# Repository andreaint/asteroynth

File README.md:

# asteroynth
a playful open synth

List of components:
https://www.mouser.com/ProjectManager/ProjectDetail.aspx?AccessID=de6c1d56a3

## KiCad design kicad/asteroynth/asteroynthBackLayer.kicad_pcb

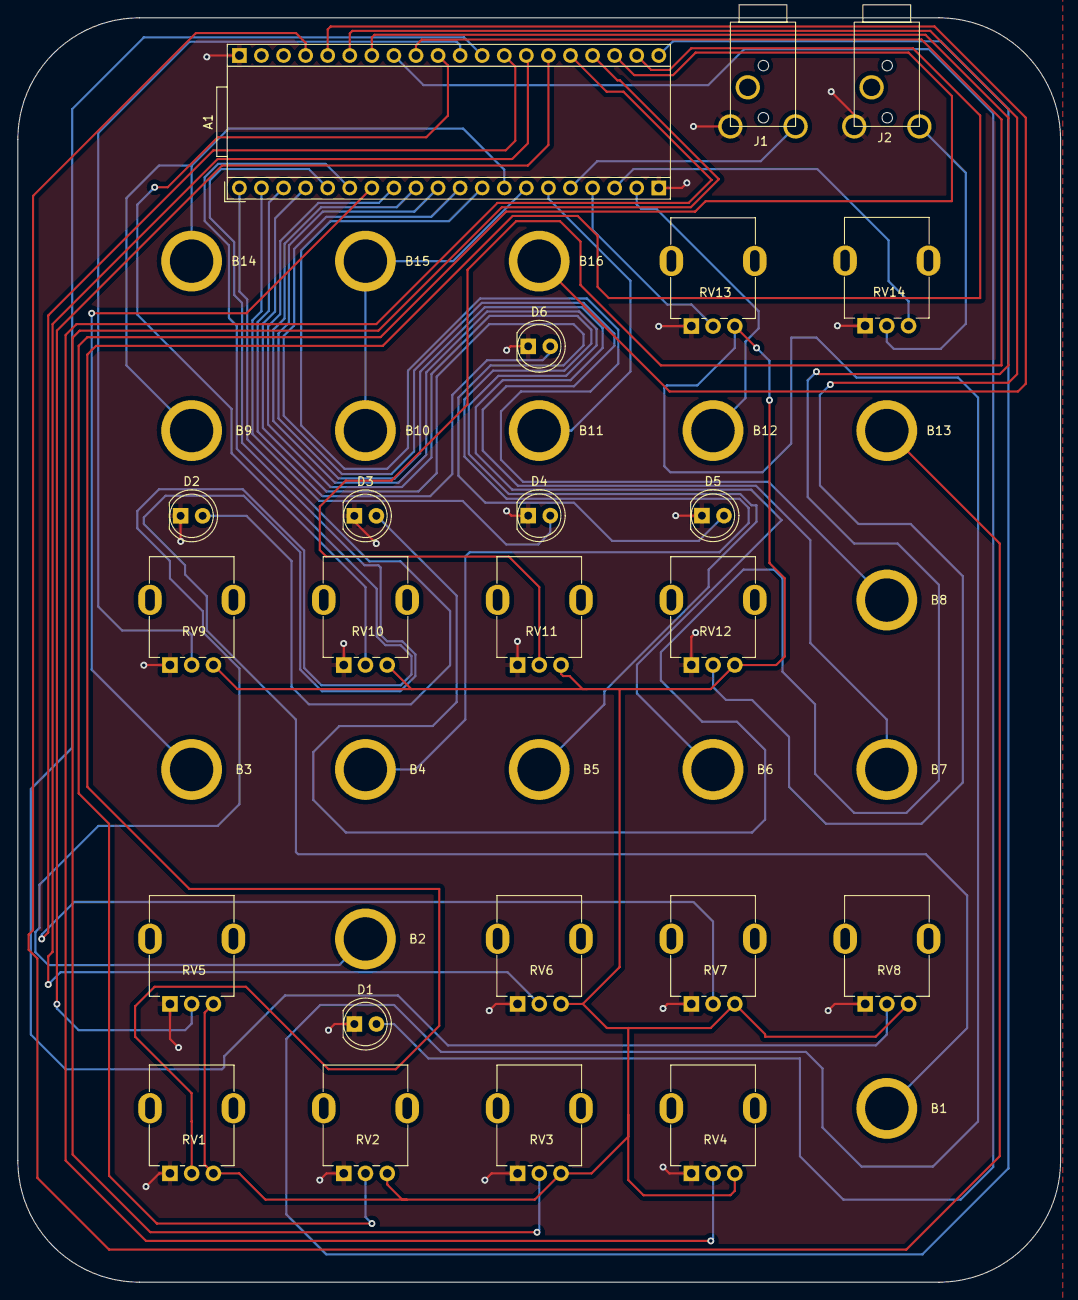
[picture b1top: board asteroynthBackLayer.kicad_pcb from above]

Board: 2 copper layers, 120.0 x 145.5 mm, 39 parts (0 on the bottom side), 38 nets.

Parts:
A1: Device_Audio_Electrosmith_Daisy_Seed_Rev4; Device_Audio_Electrosmith_Daisy_Seed
B1, B2, B3, B4, B5, B6, B7, B8, B9, B10, B11, B12, B13, B14, B15, B16: MyBananaJack; MyBananaJackFootprint
D1, D2, D3, D4, D5, D6: LED; LED_D5.0mm
J1: Audio In; audioJackFootprint
J2: Audio Out; audioJackFootprint
RV1, RV2, RV3, RV4, RV5, RV6, RV7, RV8, RV9, RV10, RV11, RV12, RV13, RV14: R_Potentiometer; MyPotType1Footprint

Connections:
+3V3: A1.21 (3V3_A), RV1.3, RV2.3, RV3.3, RV4.3, RV5.3, RV6.3, RV7.3, RV8.3, RV9.3, RV10.3, RV11.3, RV12.3, RV13.3
GND: A1.20 (AGND), A1.40 (GND), D1.1 (K), D2.1 (K), D3.1 (K), D4.1 (K), D5.1 (K), D6.1 (K), J1.S, J2.S, RV1.1, RV2.1, RV3.1, RV4.1, RV5.1, RV6.1, RV7.1, RV8.1, RV9.1, RV10.1, RV11.1, RV12.1, RV13.1, RV14.1
unnamed: A1.1 (USB_HS_ID), D2.2 (A)
unnamed: A1.2 (SDMMC1_D3), D4.2 (A)
unnamed: A1.3 (SDMMC1_D2), D6.2 (A)
unnamed: A1.4 (SDMMC1_D1), D5.2 (A)
unnamed: A1.5 (SDMMC1_D0), B1.0
unnamed: A1.6 (SDMMC1_CMD), B2.0
unnamed: A1.7 (SDMMC1_CK), B3.0
unnamed: A1.8 (SPI1_NSS), B4.0
unnamed: A1.9 (SPI1_SCK), B5.0
unnamed: A1.10 (SPI1_MISO), B6.0
unnamed: A1.11 (SPI1_MOSI), B7.0
unnamed: A1.12 (I2C1_SCL), B8.0
unnamed: A1.13 (I2C1_SDA), B9.0, B14.0
unnamed: A1.14 (USART1_TX), B10.0, B15.0
unnamed: A1.15 (USART1_RX), B11.0
unnamed: A1.16 (AUDIO_IN_L), J1.T
unnamed: A1.17 (AUDIO_IN_R), RV13.2
unnamed: A1.18 (AUDIO_OUT_L), RV14.3
unnamed: A1.19 (AUDIO_OUT_R), B12.0
unnamed: A1.22 (ADC_INP10), RV1.2
unnamed: A1.23 (ADC_INP15), RV2.2
unnamed: A1.24 (ADC_INP5), RV3.2
unnamed: A1.25 (ADC_INP7), RV4.2
unnamed: A1.26 (ADC_INP3), RV5.2
unnamed: A1.27 (ADC_INP11), RV6.2
unnamed: A1.28 (ADC1_INP4), RV7.2
unnamed: A1.29 (DAC1_OUT2), RV8.2
unnamed: A1.30 (DAC1_OUT1), RV9.2
unnamed: A1.31 (SAI2_MCLK_B), RV10.2
unnamed: A1.32 (SAI2_SD_B), RV11.2
unnamed: A1.33 (SAI2_SD_A), D1.2 (A)
unnamed: A1.34 (SAI2_FS_B), D3.2 (A)
unnamed: A1.35 (SAI2_SCK_B), RV12.2
unnamed: A1.36 (USB_HS_D_-), B16.0
unnamed: A1.37 (USB_HS_D_+), B13.0
unnamed: J2.T, RV14.2

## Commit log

2023-01-22 uploading
